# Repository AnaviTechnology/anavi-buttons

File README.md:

# anavi-buttons
Simple add-on board with 3 buttons for Raspberry Pi and Arduino

# License

The project is released under the [Creative Commons Attribution-ShareAlike 4.0 International (CC BY-SA 4.0)](https://creativecommons.org/licenses/by-sa/4.0/).

Note: This is a human-readable summary of (and not a substitute for) the [license](https://creativecommons.org/licenses/by-sa/4.0/legalcode).

You are free to:

Share — copy and redistribute the material in any medium or format Adapt — remix, transform, and build upon the material for any purpose, even commercially. The licensor cannot revoke these freedoms as long as you follow the license terms. Under the following terms:

Attribution — You must give appropriate credit, provide a link to the license, and indicate if changes were made. You may do so in any reasonable manner, but not in any way that suggests the licensor endorses you or your use. ShareAlike — If you remix, transform, or build upon the material, you must distribute your contributions under the same license as the original. No additional restrictions — You may not apply legal terms or technological measures that legally restrict others from doing anything the license permits. Notices:

You do not have to comply with the license for elements of the material in the public domain or where your use is permitted by an applicable exception or limitation. No warranties are given. The license may not give you all of the permissions necessary for your intended use. For example, other rights such as publicity, privacy, or moral rights may limit how you use the material.

You will have to provide a link to the original creator of the project http://www.anavi.technology on any documentation or website.

Credit can be attributed through a link to the creator website: http://www.anavi.technology

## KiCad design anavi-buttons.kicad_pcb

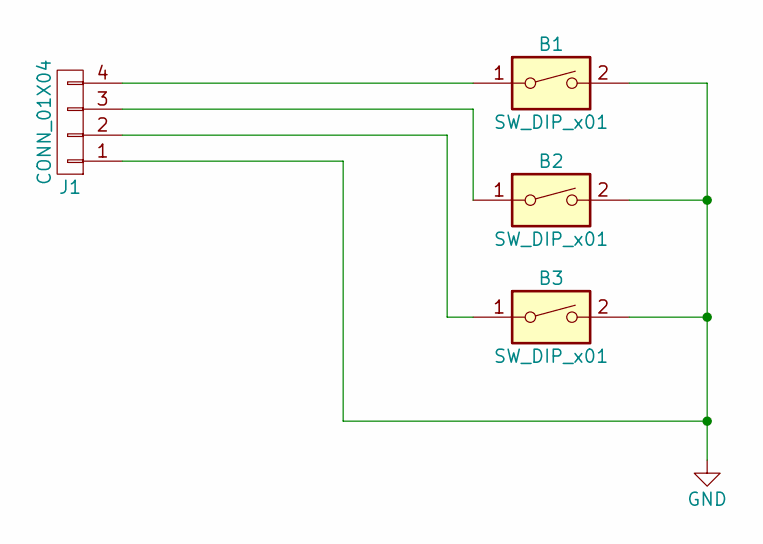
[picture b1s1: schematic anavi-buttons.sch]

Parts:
B1, B2, B3: SW_DIP_x01; SW_PUSH_6mm_h4.3mm
J1: CONN_01X04; Pin_Header_Angled_1x04_Pitch2.54mm

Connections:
GND: B1.2, B2.2, B3.2, J1.1
unnamed: B1.1, J1.4
unnamed: B2.1, J1.3
unnamed: B3.1, J1.2

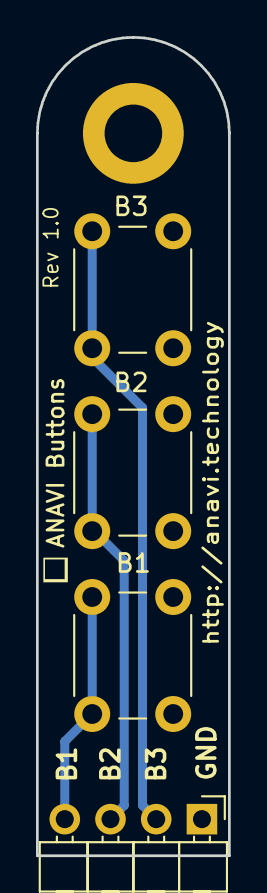
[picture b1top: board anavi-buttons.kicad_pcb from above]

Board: 2 copper layers, 10.7 x 45.5 mm, 4 parts (0 on the bottom side), 4 nets.

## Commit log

2018-07-20 anavi-buttons.kicad_pcb: Wider GND
    Extend the path that connects the GND fill zone.
    Suggested-by: Lazar Hristov <lhristov@gmail.com>
